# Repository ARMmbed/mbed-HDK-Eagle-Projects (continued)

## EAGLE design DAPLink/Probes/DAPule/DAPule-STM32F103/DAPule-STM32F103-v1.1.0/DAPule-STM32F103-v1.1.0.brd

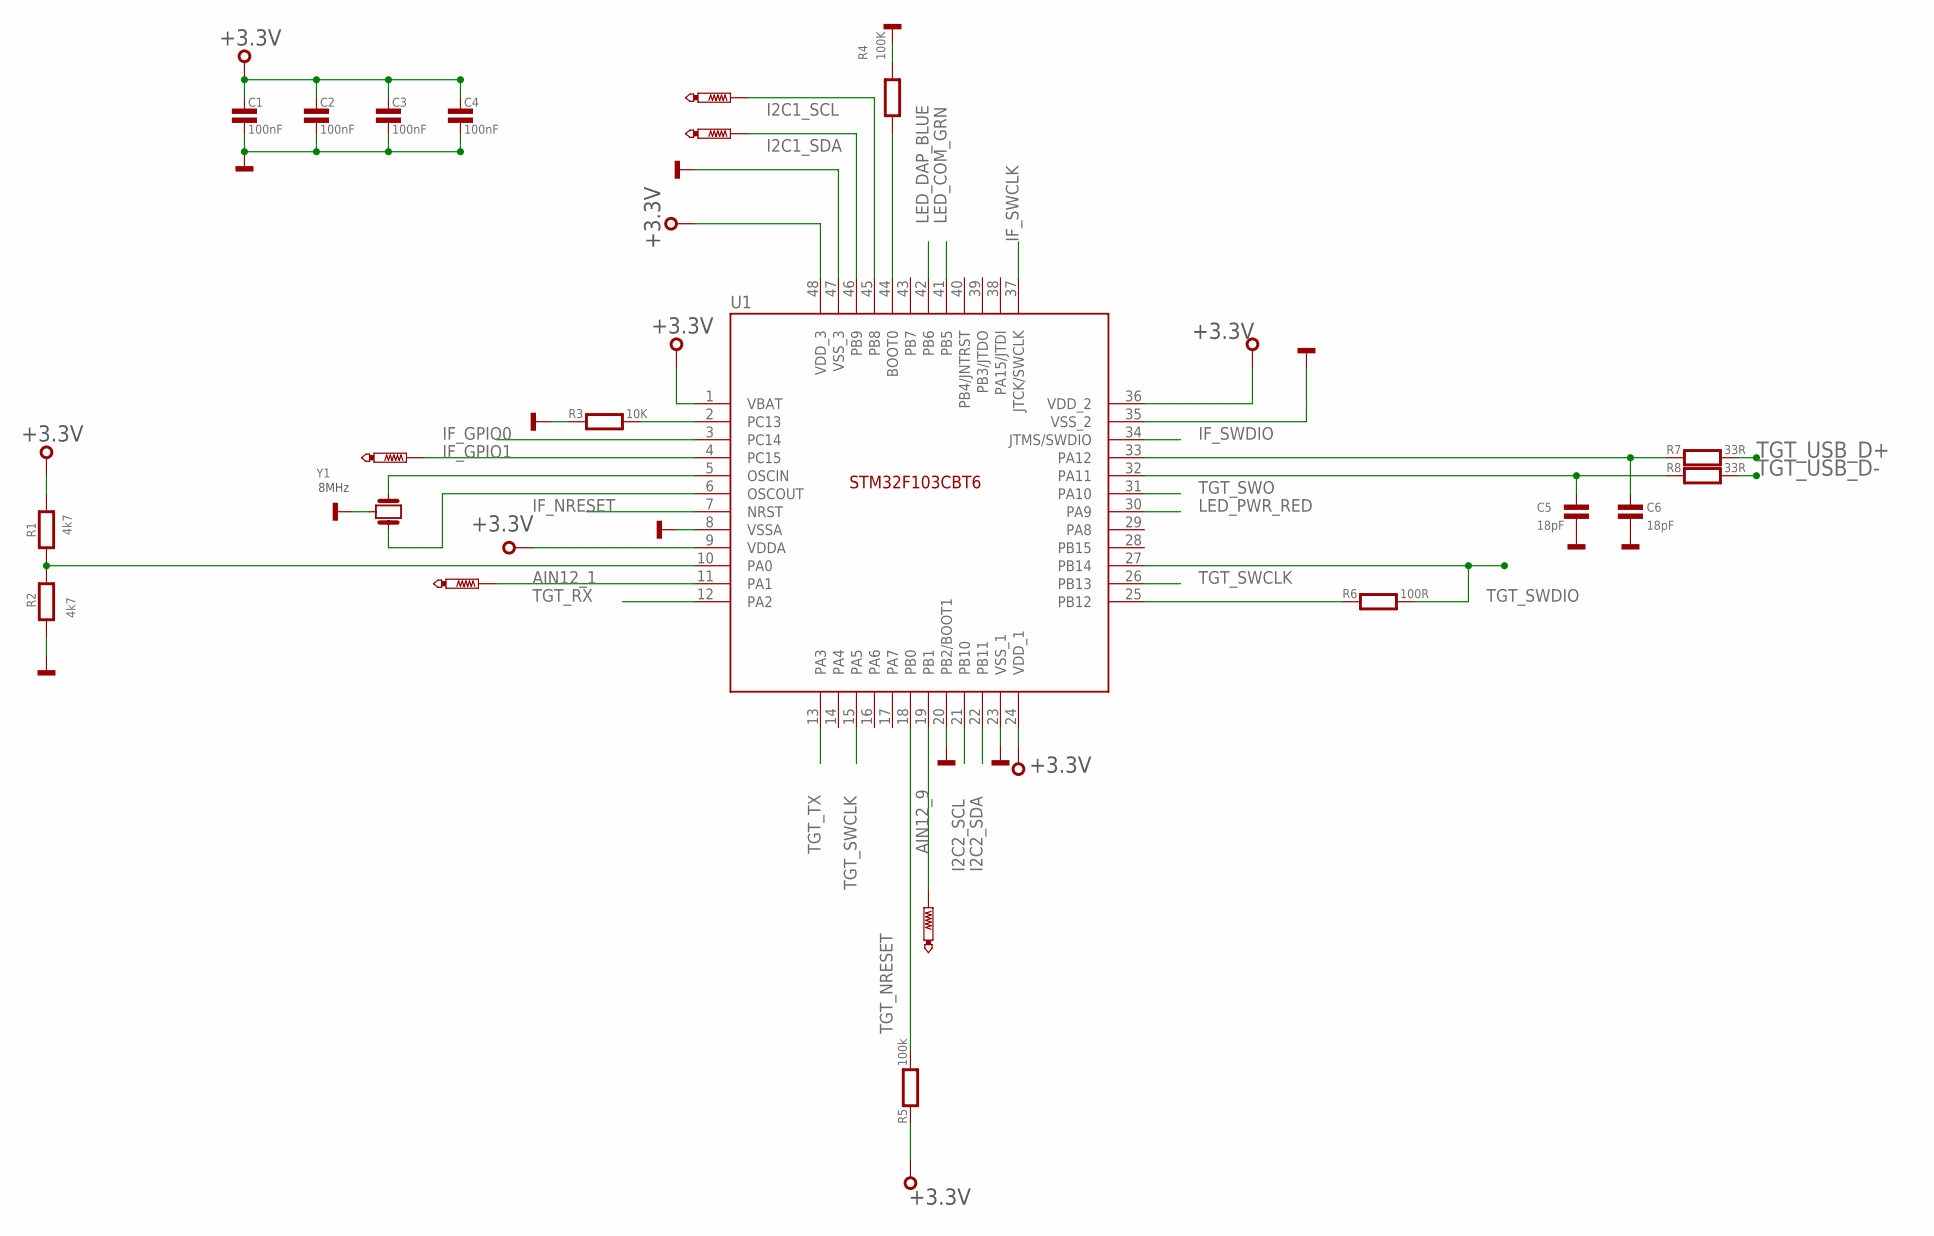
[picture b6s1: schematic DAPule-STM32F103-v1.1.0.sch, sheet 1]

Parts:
C1, C2, C3, C4: 100nF; 0603
C5, C6: 18pF; 0603
R1, R2: 4k7; 0603
R3: 10K; 0603
R4: 100K; 0603
R5: 100k; 0603
R6: 100R; 0603
R7, R8: 33R; 0603
TP1, TP2, TP3, TP4, TP5: PTR1TP07R; TP07R
U1: STM32F103CBT6; LQFP48
Y1: CSTCE8M00G55-R0

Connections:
+3.3V: C1.1, C2.1, C3.1, C4.1, R1.1, R5.1, U1.1 (VBAT), U1.9 (VDDA), U1.24 (VDD_1), U1.36 (VDD_2), U1.48 (VDD_3); also elsewhere on the board
AIN12_1: TP2.TP, U1.11 (PA1)
AIN12_9: TP1.TP, U1.19 (PB1)
GND: C1.2, C2.2, C3.2, C4.2, C5.2, C6.2, R2.2, R3.1, R4.1, U1.8 (VSSA), U1.20 (PB2/BOOT1), U1.23 (VSS_1), U1.35 (VSS_2), U1.47 (VSS_3), Y1.2; also elsewhere on the board
I2C1_SCL: TP4.TP, U1.45 (PB8)
I2C1_SDA: TP5.TP, U1.46 (PB9)
I2C2_SCL: U1.21 (PB10); also elsewhere on the board
I2C2_SDA: U1.22 (PB11); also elsewhere on the board
IF_GPIO0: U1.3 (PC14); also elsewhere on the board
IF_GPIO1: TP3.TP, U1.4 (PC15)
IF_NRESET: U1.7 (NRST); also elsewhere on the board
IF_SWCLK: U1.37 (JTCK/SWCLK); also elsewhere on the board
IF_SWDIO: U1.34 (JTMS/SWDIO); also elsewhere on the board
LED_COM_GRN: U1.41 (PB5); also elsewhere on the board
LED_DAP_BLUE: U1.42 (PB6); also elsewhere on the board
LED_PWR_RED: U1.30 (PA9); also elsewhere on the board
unnamed: R4.2, U1.44 (BOOT0)
unnamed: R3.2, U1.2 (PC13)
unnamed: U1.6 (OSCOUT), Y1.3
unnamed: U1.5 (OSCIN), Y1.1
unnamed: R1.2, R2.1, U1.10 (PA0)
unnamed: R6.1, U1.25 (PB12)
unnamed: C6.1, R7.1, U1.33 (PA12)
unnamed: C5.1, R8.1, U1.32 (PA11)
TGT_NRESET: R5.2, U1.18 (PB0); also elsewhere on the board
TGT_RX: U1.12 (PA2); also elsewhere on the board
TGT_SWCLK: U1.15 (PA5), U1.26 (PB13); also elsewhere on the board
TGT_SWDIO: R6.2, U1.27 (PB14); also elsewhere on the board
TGT_SWO: U1.31 (PA10); also elsewhere on the board
TGT_TX: U1.13 (PA3); also elsewhere on the board
TGT_USB_D+: R7.2; also elsewhere on the board
TGT_USB_D-: R8.2; also elsewhere on the board

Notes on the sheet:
8MHz

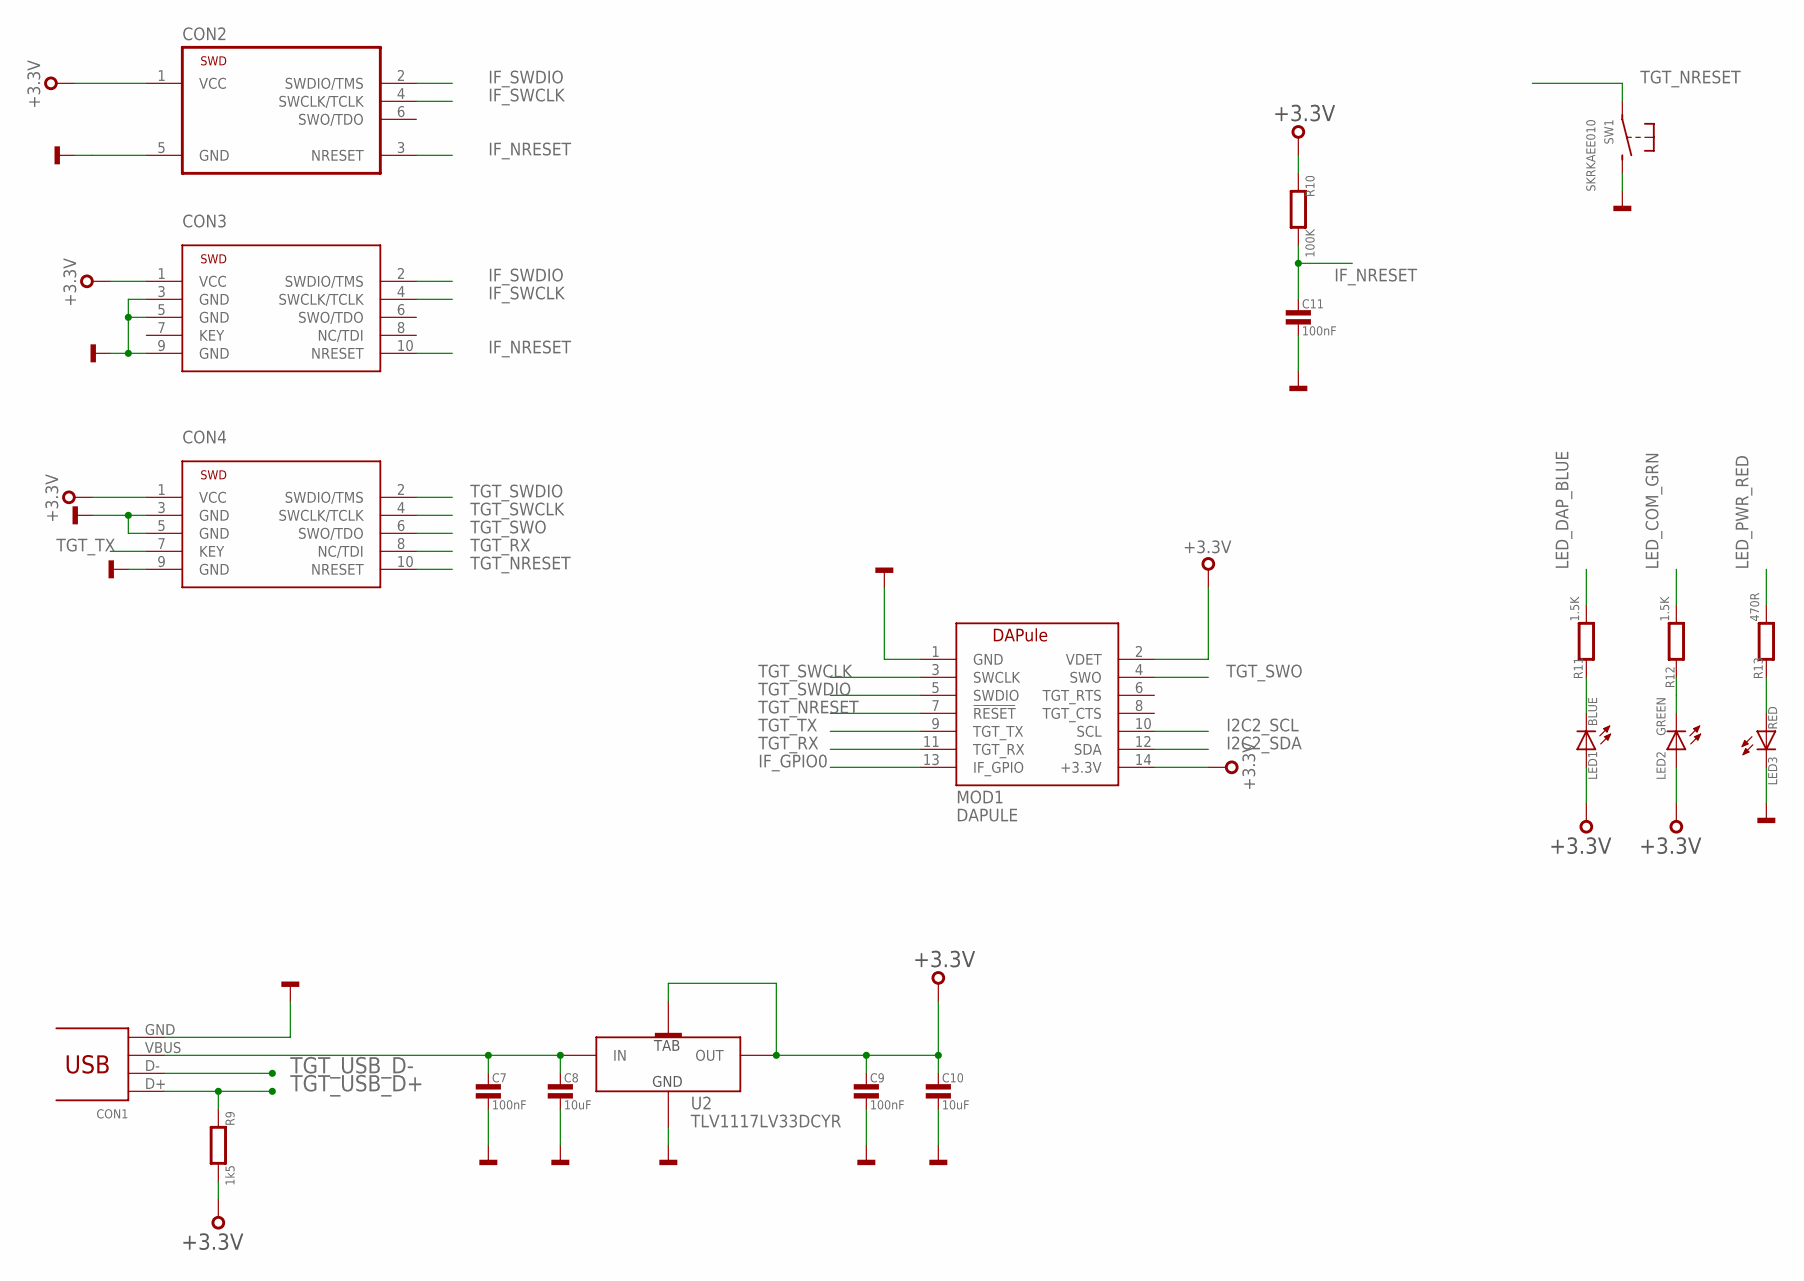
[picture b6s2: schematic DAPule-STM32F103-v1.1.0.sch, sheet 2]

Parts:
C7, C9, C11: 100nF; 0603
C8, C10: 10uF; 0603
CON1: 47346-0001; USB-MICRO-B-H
CON2: TC2030-CTX-NL
CON3, CON4: SWD-10-SMD
LED1: BLUE; CHIPLED_0603
LED2: GREEN; CHIPLED_0603
LED3: RED; CHIPLED_0603
MOD1: DAPULE
R9: 1k5; 0603
R10: 100K; 0603
R11, R12: 1.5K; 0603
R13: 470R; 0603
SW1: SKRKAEE010
U2: TLV1117LV33DCYR; SOT223

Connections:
+3.3V: C9.1, C10.1, CON2.1 (VCC), CON3.1 (VCC), CON4.1 (VCC), LED1.A, LED2.A, MOD1.2 (VDET), MOD1.14 (+3.3V), R9.2, R10.1, U2.OUT(1) (OUT), U2.OUT(2) (TAB); also elsewhere on the board
GND: C7.2, C8.2, C9.2, C10.2, C11.2, CON1.GND, CON2.5 (GND), CON3.3 (GND), CON3.5 (GND), CON3.9 (GND), CON4.3 (GND), CON4.5 (GND), CON4.9 (GND), LED3.C, MOD1.1 (GND), SW1.P$2 (S), U2.GND; also elsewhere on the board
I2C2_SCL: MOD1.10 (SCL); also elsewhere on the board
I2C2_SDA: MOD1.12 (SDA); also elsewhere on the board
IF_GPIO0: MOD1.13 (IF_GPIO); also elsewhere on the board
IF_NRESET: C11.1, CON2.3 (NRESET), CON3.10 (NRESET), R10.2; also elsewhere on the board
IF_SWCLK: CON2.4 (SWCLK/TCLK), CON3.4 (SWCLK/TCLK); also elsewhere on the board
IF_SWDIO: CON2.2 (SWDIO/TMS), CON3.2 (SWDIO/TMS); also elsewhere on the board
LED_COM_GRN: R12.2; also elsewhere on the board
LED_DAP_BLUE: R11.2; also elsewhere on the board
LED_PWR_RED: R13.2; also elsewhere on the board
unnamed: C7.1, C8.1, CON1.VBUS, U2.IN
unnamed: LED3.A, R13.1
unnamed: LED1.C, R11.1
unnamed: LED2.C, R12.1
TGT_NRESET: CON4.10 (NRESET), MOD1.7 (!RESET), SW1.P$1; also elsewhere on the board
TGT_RX: CON4.8 (NC/TDI), MOD1.11 (TGT_RX); also elsewhere on the board
TGT_SWCLK: CON4.4 (SWCLK/TCLK), MOD1.3 (SWCLK); also elsewhere on the board
TGT_SWDIO: CON4.2 (SWDIO/TMS), MOD1.5 (SWDIO); also elsewhere on the board
TGT_SWO: CON4.6 (SWO/TDO), MOD1.4 (SWO); also elsewhere on the board
TGT_TX: CON4.7 (KEY), MOD1.9 (TGT_TX); also elsewhere on the board
TGT_USB_D+: CON1.D+, R9.1; also elsewhere on the board
TGT_USB_D-: CON1.D-; also elsewhere on the board

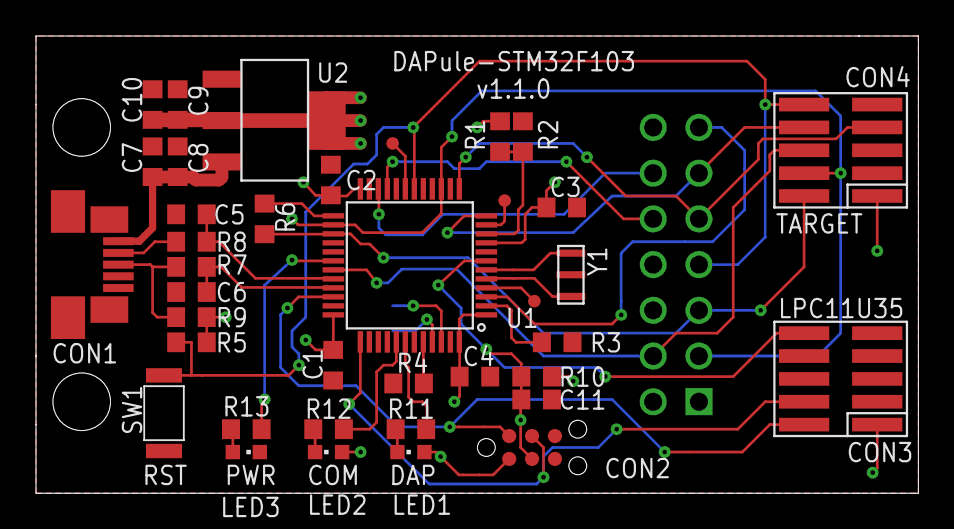
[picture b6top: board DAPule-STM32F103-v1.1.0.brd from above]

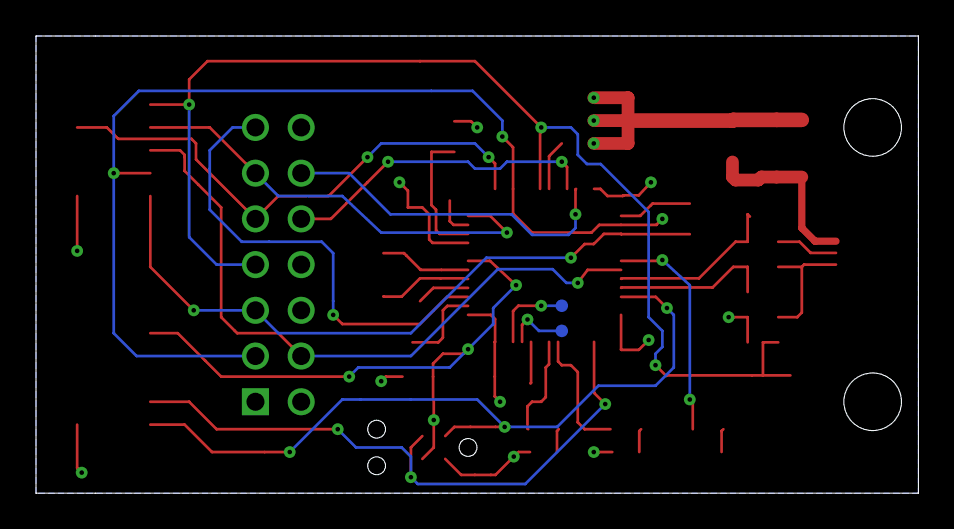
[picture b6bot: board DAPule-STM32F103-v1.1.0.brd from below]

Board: 2 copper layers, 49.0 x 25.4 mm, 41 parts (2 on the bottom side), 36 nets.

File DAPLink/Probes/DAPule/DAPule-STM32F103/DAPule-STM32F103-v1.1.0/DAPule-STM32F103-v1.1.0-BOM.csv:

"Qty";"Value";"Device";"Package";"Parts";"Description";"MF";"MFN";"OC-DIGIKEY";"OC-MOUSER";"OC-NEWARK";"TP_SIGNAL_NAME";
"2";"1.5K";"R0603";"0603";"R11, R12";"Resistor";"";"";"";"";"";"";
"2";"100K";"R0603";"0603";"R4, R10";"Resistor";"";"";"";"";"";"";
"1";"100R";"R0603";"0603";"R6";"Resistor";"";"";"";"";"";"";
"1";"100k";"R0603";"0603";"R5";"Resistor";"";"";"";"";"";"";
"7";"100nF";"C0603";"0603";"C1, C2, C3, C4, C7, C9, C11";"Capacitor";"";"";"";"";"";"";
"1";"10K";"R0603";"0603";"R3";"Resistor";"";"";"";"";"";"";
"2";"10uF";"C0603";"0603";"C8, C10";"Capacitor";"";"";"";"";"";"";
"2";"18pF";"C0603";"0603";"C5, C6";"Capacitor";"";"";"";"";"";"";
"1";"1k5";"R0603";"0603";"R9";"Resistor";"";"";"";"";"";"";
"2";"33R";"R0603";"0603";"R7, R8";"Resistor";"";"";"";"";"";"";
"1";"470R";"R0603";"0603";"R13";"Resistor";"";"";"";"";"";"";
"1";"47346-0001";"47346-0001";"USB-MICRO-B-H";"CON1";"USB Receptacle Horizontal Micro Type B";"MOLEX";"47346-0001";"";"538-47346-0001";"1568026";"";
"2";"4k7";"R0603";"0603";"R1, R2";"Resistor";"";"";"";"";"";"";
"1";"BLUE";"SMD_LED0603";"CHIPLED_0603";"LED1";"LED SMD, Colour Red";"Wurth Electronics Inc";"150060RS75000";"732-4978-1-ND";"710-150060RS75000";"2322071";"";
"1";"CSTCE8M00G55-R0";"CSTCE8M00G55-R0";"CSTCE8M00G55-R0";"Y1";"Resonator Cermanic, Murata 8MHz 33pF";"Murata";"CSTCE8M00G55-R0";"490-1195-1-ND";"81-CSTCE8M00G55-R0";"2443270";"";
"1";"DAPULE";"DAPULE";"DAPULE";"MOD1";"";"";"";"";"";"";"";
"1";"GREEN";"SMD_LED0603";"CHIPLED_0603";"LED2";"LED SMD, Colour Red";"Wurth Electronics Inc";"150060RS75000";"732-4978-1-ND";"710-150060RS75000";"2322071";"";
"5";"PTR1TP07R";"PTR1TP07R";"TP07R";"TP1, TP2, TP3, TP4, TP5";"TEST PIN";"";"";"";"";"";"";
"1";"RED";"SMD_LED0603";"CHIPLED_0603";"LED3";"LED SMD, Colour Red";"Wurth Electronics Inc";"150060RS75000";"732-4978-1-ND";"710-150060RS75000";"2322071";"";
"1";"SKRKAEE010";"SKRKAEE010";"SKRKAEE010";"SW1";"MOMENTARY SWITCH PUSH VERTICAL (SPST)";"ALPS";"SKRKAEE010";"";"688-SKRKAE";"";"";
"1";"STM32F103CBT6";"STM32F103CBT6";"LQFP48";"U1";"ARM® Cortex®-M3 STM32 F1 Microcontroller IC 32-Bit 72MHz 128KB (128K x 8) FLASH";"STMicroelectronics";"STM32F103CBT6";"497-6288-ND";"511-STM32F103CBT6";"11N8296";"";
"2";"SWD-10-SMD";"SWD-10-SMD";"SWD-10-SMD";"CON3, CON4";"2.54mm pitch 10-Pin Cortex Programming Header";"";"";"";"";"";"";
"1";"TC2030-CTX-NL";"TC2030-CTX-NL";"TC2030-CTX-NL";"CON2";"Tag-Connect In Circuit Programming & Debug Cable 6 Pin";"";"";"";"";"";"";
"1";"TLV1117LV33DCYR";"TLV1117LV33DCYR";"SOT223";"U2";"LDO Fixed Regulator 3.3v, 1A";"Texas Instruments";"TLV1117LV33DCYR";"296-28778-1-ND";"595-TLV1117LV33DCYR";"2323647";"";

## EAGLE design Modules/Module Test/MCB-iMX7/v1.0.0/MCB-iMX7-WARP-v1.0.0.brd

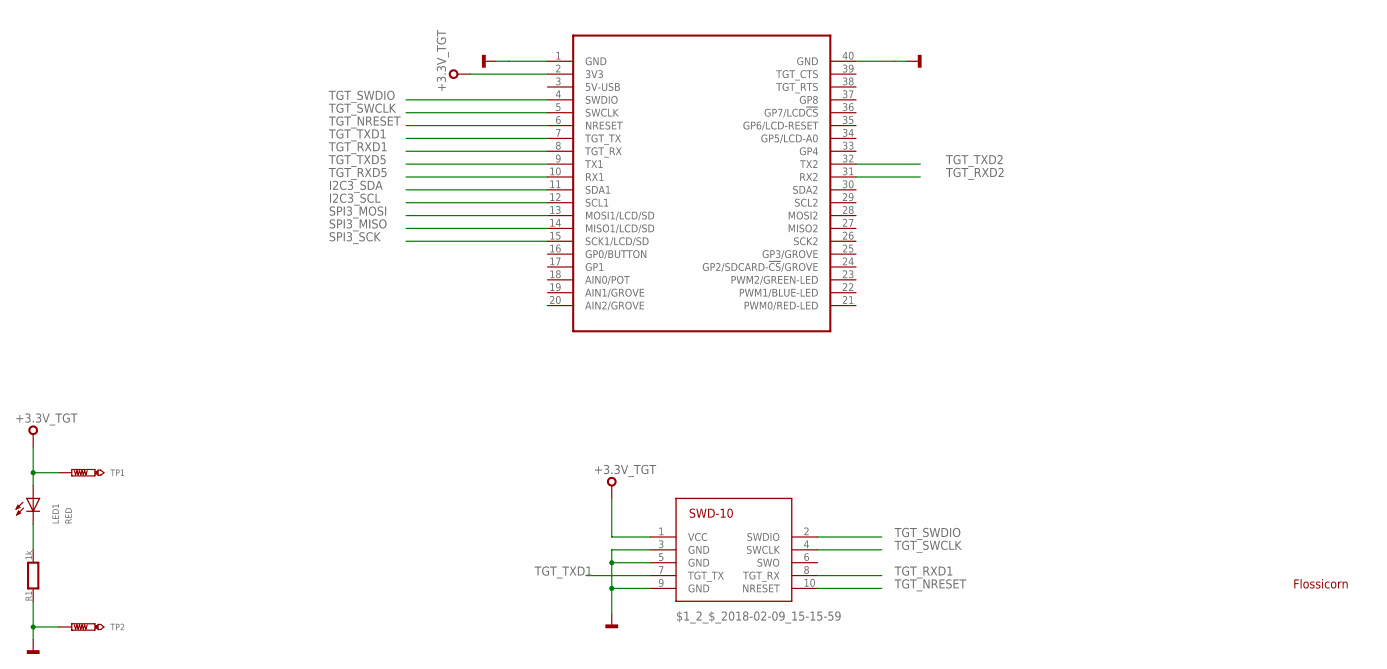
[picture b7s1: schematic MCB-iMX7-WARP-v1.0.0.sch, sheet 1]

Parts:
$1_2_$_2018-02-09_15-15-59: SWD-10/TC2050_SMD; FTSH-105-02
LED1: RED; CHIPLED_0603
MOD1: MODULE_DAUGHTER
R1: 1k; 0603
SS1: FLOSSICORN0.5; FLOSSICORN-0.5
TP1, TP2: TEST-POINT-50R-PTH; TP50-PTH

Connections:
+3.3V_TGT: $1_2_$_2018-02-09_15-15-59.1 (VCC), LED1.A, MOD1.2 (3V3), TP1.TP; also elsewhere on the board
GND: $1_2_$_2018-02-09_15-15-59.3 (GND), $1_2_$_2018-02-09_15-15-59.5 (GND), $1_2_$_2018-02-09_15-15-59.9 (GND), MOD1.1 (GND), MOD1.40 (GND), R1.1, TP2.TP; also elsewhere on the board
I2C3_SCL: MOD1.12 (SCL1); also elsewhere on the board
I2C3_SDA: MOD1.11 (SDA1); also elsewhere on the board
PA_1: LED1.C, R1.2
SPI3_MISO: MOD1.14 (MISO1/LCD/SD); also elsewhere on the board
SPI3_MOSI: MOD1.13 (MOSI1/LCD/SD); also elsewhere on the board
SPI3_SCK: MOD1.15 (SCK1/LCD/SD); also elsewhere on the board
TGT_NRESET: $1_2_$_2018-02-09_15-15-59.10 (NRESET), MOD1.6 (NRESET)
TGT_RXD1: $1_2_$_2018-02-09_15-15-59.8 (TGT_RX), MOD1.8 (TGT_RX); also elsewhere on the board
TGT_RXD2: MOD1.31 (RX2); also elsewhere on the board
TGT_RXD5: MOD1.10 (RX1); also elsewhere on the board
TGT_SWCLK: $1_2_$_2018-02-09_15-15-59.4 (SWCLK), MOD1.5 (SWCLK); also elsewhere on the board
TGT_SWDIO: $1_2_$_2018-02-09_15-15-59.2 (SWDIO), MOD1.4 (SWDIO); also elsewhere on the board
TGT_TXD1: $1_2_$_2018-02-09_15-15-59.7 (TGT_TX), MOD1.7 (TGT_TX); also elsewhere on the board
TGT_TXD2: MOD1.32 (TX2); also elsewhere on the board
TGT_TXD5: MOD1.9 (TX1); also elsewhere on the board

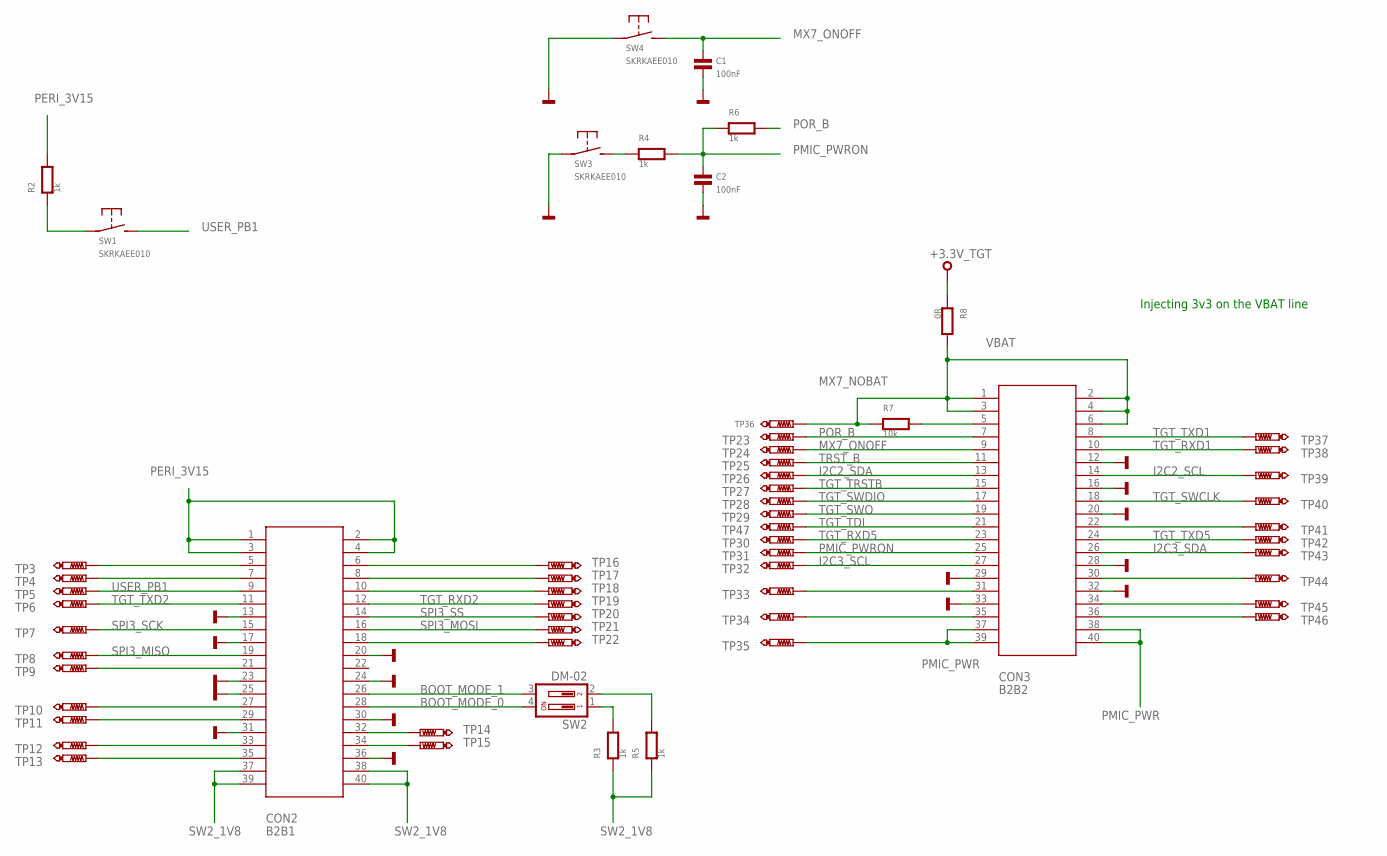
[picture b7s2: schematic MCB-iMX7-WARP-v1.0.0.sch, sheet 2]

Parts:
C1, C2: 100nF; 0603
CON2: B2B1; DF40HC-XX-40DS-XX-V
CON3: B2B2; DF40HC-XX-40DS-XX-V
R2, R3, R4, R5, R6: 1k; 0603
R7: 10k; 0603
R8: 0R; 0603
SW1, SW3, SW4: SKRKAEE010
SW2: DM-02
TP3, TP4, TP5, TP6, TP7, TP8, TP9, TP10, TP11, TP12, TP13, TP14, TP15, TP16, TP17, TP18, TP19, TP20, TP21, TP22, TP23, TP24, TP25, TP26, TP27, TP28, TP29, TP30, TP31, TP32, TP33, TP34, TP37, TP38, TP39, TP40, TP41, TP42, TP43, TP44, TP45, TP46, TP47: PTR1TP06R; TP06R
TP35: PTR1TP10R; TP10R
TP36: TEST-POINT-50R-SMD; TP50-SMD

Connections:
+3.3V_TGT: R8.1; also elsewhere on the board
BOOT_MODE_0: CON2.28, SW2.4
BOOT_MODE_1: CON2.26, SW2.3
GND: C1.2, C2.2, CON2.13, CON2.17, CON2.20, CON2.23, CON2.24, CON2.25, CON2.30, CON2.31, CON2.36, CON3.12, CON3.16, CON3.20, CON3.28, CON3.29, CON3.32, CON3.33, SW3.P$1, SW4.P$1; also elsewhere on the board
I2C2_SCL: CON3.14, TP39.TP
I2C2_SDA: CON3.13, TP26.TP
I2C3_SCL: CON3.27, TP32.TP; also elsewhere on the board
I2C3_SDA: CON3.26, TP43.TP; also elsewhere on the board
MX7_NOBAT: CON3.5, R7.2
MX7_ONOFF: C1.1, CON3.9, SW4.P$2 (S), TP24.TP
unnamed: R4.1, SW3.P$2 (S)
unnamed: R2.1, SW1.P$1
unnamed: CON3.36, TP46.TP
unnamed: CON3.22, TP41.TP
unnamed: CON3.30, TP44.TP
unnamed: CON3.34, TP45.TP
unnamed: R3.2, SW2.1
unnamed: R5.2, SW2.2
unnamed: CON3.31, TP33.TP
unnamed: CON3.35, TP34.TP
unnamed: CON2.5, TP3.TP
unnamed: CON2.7, TP4.TP
unnamed: CON2.21, TP9.TP
unnamed: CON2.27, TP10.TP
unnamed: CON2.29, TP11.TP
unnamed: CON2.33, TP12.TP
unnamed: CON2.35, TP13.TP
unnamed: CON2.34, TP15.TP
unnamed: CON2.32, TP14.TP
unnamed: CON2.18, TP22.TP
unnamed: CON2.10, TP18.TP
unnamed: CON2.8, TP17.TP
unnamed: CON2.6, TP16.TP
PERI_3V15: CON2.1, CON2.2, CON2.3, CON2.4, R2.2
PMIC_PWR: CON3.37, CON3.38, CON3.39, CON3.40, TP35.TP
PMIC_PWRON: C2.1, CON3.25, R4.2, R6.1, TP31.TP
POR_B: CON3.7, R6.2, TP23.TP
SPI3_MISO: CON2.19, TP8.TP; also elsewhere on the board
SPI3_MOSI: CON2.16, TP21.TP; also elsewhere on the board
SPI3_SCK: CON2.15, TP7.TP; also elsewhere on the board
SPI3_SS: CON2.14, TP20.TP
SW2_1V8: CON2.37, CON2.38, CON2.39, CON2.40, R3.1, R5.1
TGT_RXD1: CON3.10, TP38.TP; also elsewhere on the board
TGT_RXD2: CON2.12, TP19.TP; also elsewhere on the board
TGT_RXD5: CON3.23, TP30.TP; also elsewhere on the board
TGT_SWCLK: CON3.18, TP40.TP; also elsewhere on the board
TGT_SWDIO: CON3.17, TP28.TP; also elsewhere on the board
TGT_SWO: CON3.19, TP29.TP
TGT_TDI: CON3.21, TP47.TP
TGT_TRSTB: CON3.15, TP27.TP
TGT_TXD1: CON3.8, TP37.TP; also elsewhere on the board
TGT_TXD2: CON2.11, TP6.TP; also elsewhere on the board
TGT_TXD5: CON3.24, TP42.TP; also elsewhere on the board
TRST_B: CON3.11, TP25.TP
USER_PB1: CON2.9, SW1.P$2 (S), TP5.TP
VBAT: CON3.1, CON3.2, CON3.3, CON3.4, CON3.6, R7.1, R8.2, TP36.TP

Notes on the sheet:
Injecting 3v3 on the VBAT line

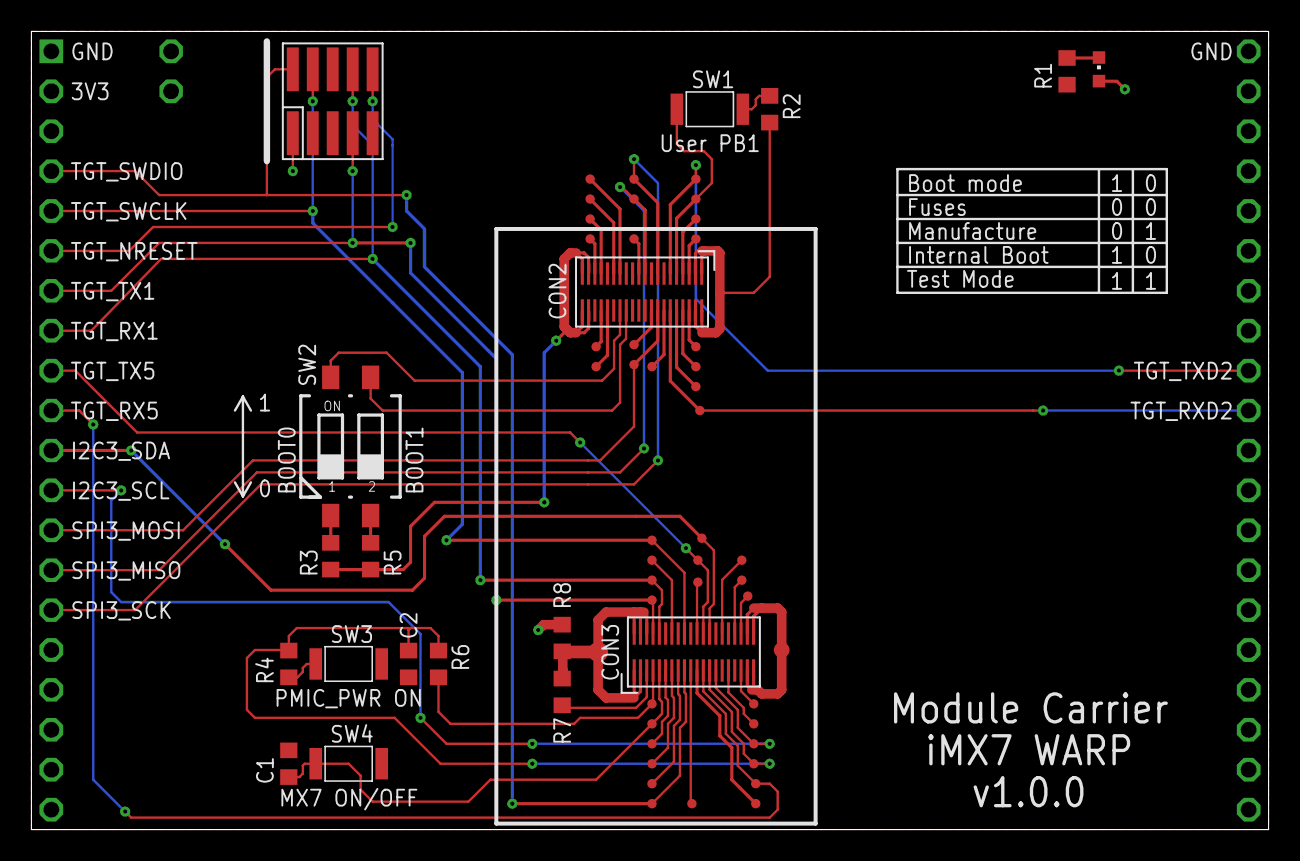
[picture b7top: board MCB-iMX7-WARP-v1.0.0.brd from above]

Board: 2 copper layers, 78.7 x 50.8 mm, 67 parts (0 on the bottom side), 58 nets.

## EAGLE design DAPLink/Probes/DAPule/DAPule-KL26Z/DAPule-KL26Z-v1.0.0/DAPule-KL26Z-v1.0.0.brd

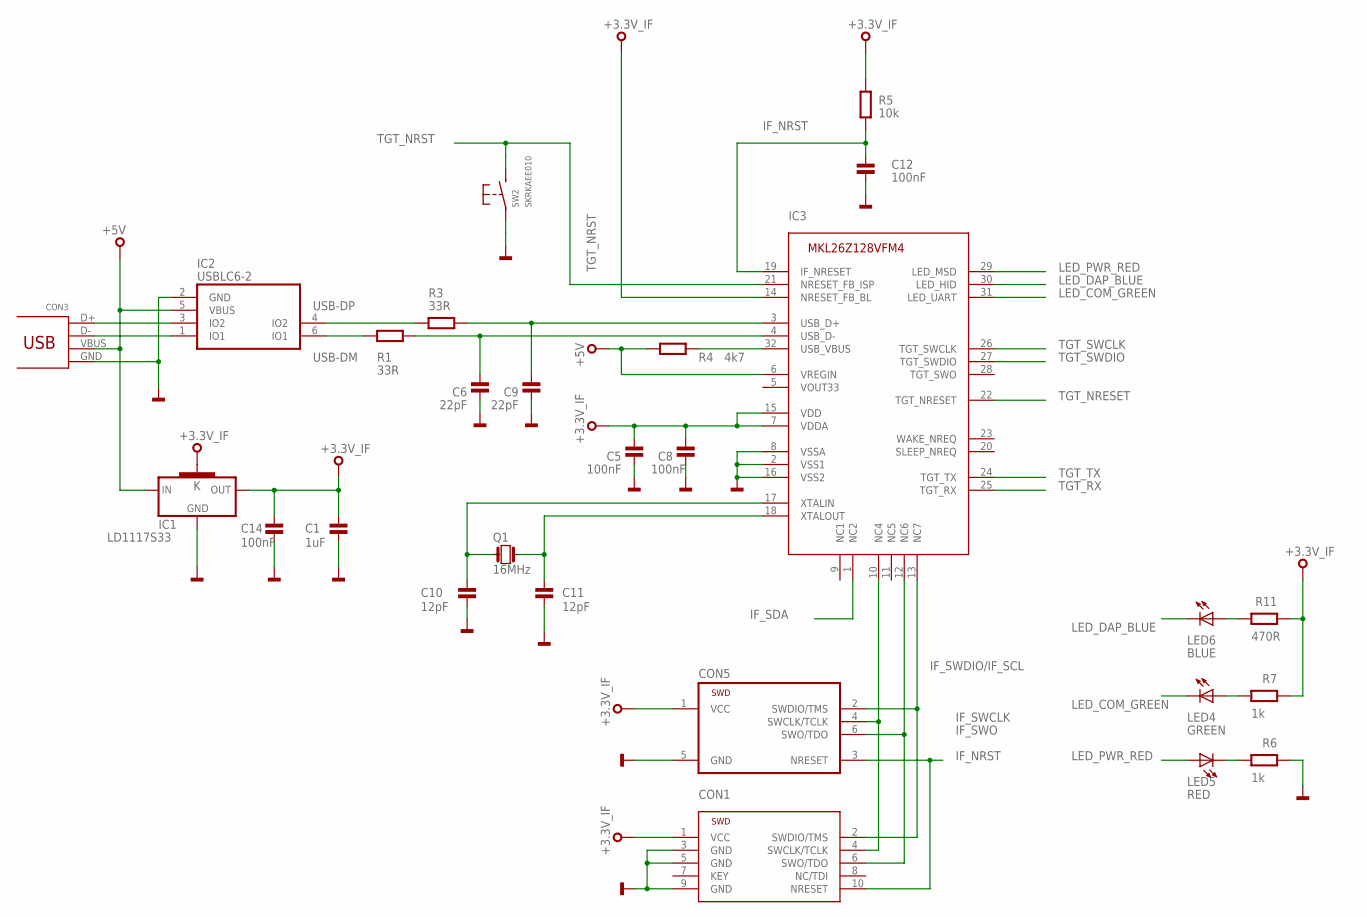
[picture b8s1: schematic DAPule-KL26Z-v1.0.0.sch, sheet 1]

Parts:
C1: 1uF; 0603
C5, C8, C12, C14: 100nF; 0603
C6, C9: 22pF; 0603
C10, C11: 12pF; 0603
CON1: SWD-10-SMD
CON3: USB_MICROB; MOLEX-47364-0001
CON5: TC2030-CTX-NL
IC1: LD1117S33; SOT223
IC2: USBLC6-2SC6; SOT23-6L
IC3: IF_MKL26Z128VFM4; HVQFN32
LED4: GREEN; CHIPLED_0603
LED5: RED; CHIPLED_0603
LED6: BLUE; CHIPLED_0603
Q1: 16MHz; 2.5X2.0
R1, R3: 33R; 0603@1
R4: 4k7; 0603@1
R5: 10k; 0603@1
R6, R7: 1k; 0603@1
R11: 470R; 0603@1
SW2: SKRKAEE010

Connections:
+3.3V_IF: C1.1, C5.2, C8.2, C14.1, CON1.1 (VCC), CON5.1 (VCC), IC1.2 (OUT), IC1.4 (K), IC3.7 (VDDA), IC3.14 (NRESET_FB_BL), IC3.15 (VDD), R5.2, R7.1, R11.1; also elsewhere on the board
+5V: CON3.VBUS, IC1.3 (IN), IC2.5 (VBUS), IC3.6 (VREGIN), R4.1
DM: CON3.D-, IC2.1 (IO1)
DP: CON3.D+, IC2.3 (IO2)
GND: C1.2, C5.1, C6.1, C8.1, C9.1, C10.1, C11.1, C12.1, C14.2, CON1.3 (GND), CON1.5 (GND), CON1.9 (GND), CON3.GND, CON5.5 (GND), IC1.1 (GND), IC2.2 (GND), IC3.2 (VSS1), IC3.8 (VSSA), IC3.16 (VSS2), R6.1, SW2.P$1; also elsewhere on the board
IF_NRST: C12.2, CON1.10 (NRESET), CON5.3 (NRESET), IC3.19 (IF_NRESET), R5.1
IF_SDA: IC3.1 (NC2); also elsewhere on the board
IF_SWCLK: CON1.4 (SWCLK/TCLK), CON5.4 (SWCLK/TCLK), IC3.10 (NC4)
IF_SWDIO/IF_SCL: CON1.2 (SWDIO/TMS), CON5.2 (SWDIO/TMS), IC3.13 (NC7); also elsewhere on the board
IF_SWO: CON1.6 (SWO/TDO), CON5.6 (SWO/TDO), IC3.12 (NC6)
LED_COM_GREEN: IC3.31 (LED_UART), LED4.C
LED_DAP_BLUE: IC3.30 (LED_HID), LED6.C
LED_PWR_RED: IC3.29 (LED_MSD), LED5.A
unnamed: IC3.32 (USB_VBUS), R4.2
unnamed: LED6.A, R11.2
unnamed: LED4.A, R7.2
unnamed: C6.2, IC3.4 (USB_D-), R1.1
unnamed: C10.2, IC3.17 (XTALIN), Q1.1
unnamed: C11.2, IC3.18 (XTALOUT), Q1.3 (2)
unnamed: C9.2, IC3.3 (USB_D+), R3.1
unnamed: LED5.C, R6.2
TGT_NRESET: IC3.22 (TGT_NRESET); also elsewhere on the board
TGT_NRST: IC3.21 (NRESET_FB_ISP), SW2.P$2 (S)
TGT_RX: IC3.25 (TGT_RX); also elsewhere on the board
TGT_SWCLK: IC3.26 (TGT_SWCLK); also elsewhere on the board
TGT_SWDIO: IC3.27 (TGT_SWDIO); also elsewhere on the board
TGT_TX: IC3.24 (TGT_TX); also elsewhere on the board
USB-DM: IC2.6 (IO1), R1.2
USB-DP: IC2.4 (IO2), R3.2

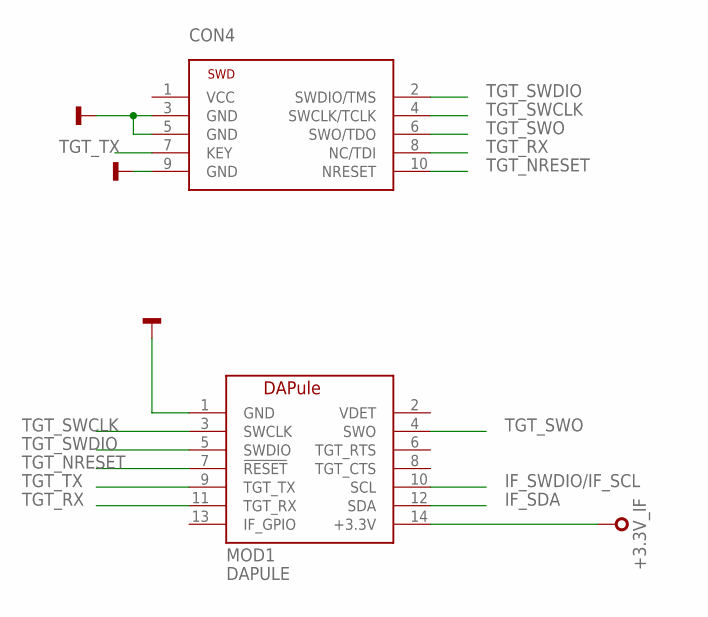
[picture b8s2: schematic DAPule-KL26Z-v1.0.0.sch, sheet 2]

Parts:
CON4: SWD-10-SMD
MOD1: DAPULE

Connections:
+3.3V_IF: MOD1.14 (+3.3V); also elsewhere on the board
GND: CON4.3 (GND), CON4.5 (GND), CON4.9 (GND), MOD1.1 (GND); also elsewhere on the board
IF_SDA: MOD1.12 (SDA); also elsewhere on the board
IF_SWDIO/IF_SCL: MOD1.10 (SCL); also elsewhere on the board
TGT_NRESET: CON4.10 (NRESET), MOD1.7 (!RESET); also elsewhere on the board
TGT_RX: CON4.8 (NC/TDI), MOD1.11 (TGT_RX); also elsewhere on the board
TGT_SWCLK: CON4.4 (SWCLK/TCLK), MOD1.3 (SWCLK); also elsewhere on the board
TGT_SWDIO: CON4.2 (SWDIO/TMS), MOD1.5 (SWDIO); also elsewhere on the board
TGT_SWO: CON4.6 (SWO/TDO), MOD1.4 (SWO)
TGT_TX: CON4.7 (KEY), MOD1.9 (TGT_TX); also elsewhere on the board

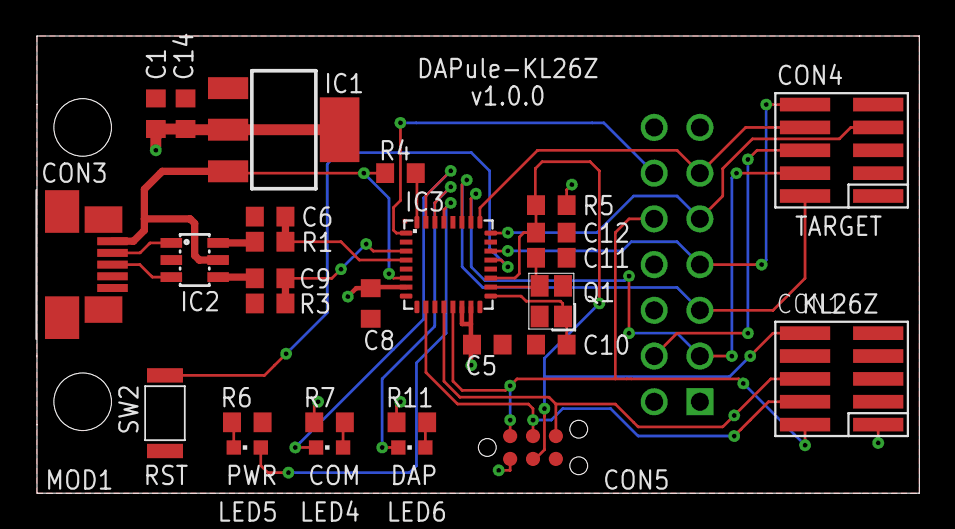
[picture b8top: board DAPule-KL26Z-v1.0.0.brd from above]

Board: 2 copper layers, 49.1 x 25.4 mm, 29 parts (0 on the bottom side), 30 nets.

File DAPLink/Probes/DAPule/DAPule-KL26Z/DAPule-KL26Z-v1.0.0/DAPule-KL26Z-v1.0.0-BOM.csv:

"Qty";"Value";"Device";"Package";"Parts";"Description";"MF";"MFN";"OC-DIGIKEY";"OC-MOUSER";"OC-NEWARK";
"4";"100nF";"C0603";"0603";"C5, C8, C12, C14";"Capacitor";"";"";"";"";"";
"1";"10k";"R0603";"0603@1";"R5";"";"";"";"";"";"";
"2";"12pF";"C0603";"0603";"C10, C11";"Capacitor";"";"";"";"";"";
"1";"16MHz";"Q_2.5X2.0";"2.5X2.0";"Q1";"";"";"";"";"";"";
"2";"1k";"R0603";"0603@1";"R6, R7";"";"";"";"";"";"";
"1";"1uF";"C0603";"0603";"C1";"Capacitor";"";"";"";"";"";
"2";"22pF";"C0603";"0603";"C6, C9";"Capacitor";"";"";"";"";"";
"2";"33R";"R0603";"0603@1";"R1, R3";"";"";"";"";"";"";
"1";"470R";"R0603";"0603@1";"R11";"";"";"";"";"";"";
"1";"4k7";"R0603";"0603@1";"R4";"";"";"";"";"";"";
"1";"BLUE";"LED0603";"CHIPLED_0603";"LED6";"SMD LED";"";"";"";"";"";
"1";"DAPULE";"DAPULE";"DAPULE";"MOD1";"";"";"";"";"";"";
"1";"GREEN";"LED0603";"CHIPLED_0603";"LED4";"SMD LED";"";"";"";"";"";
"1";"IF_MKL26Z128VFM4";"IF_MKL26Z128VFM4";"HVQFN32";"IC3";"CMSIS-DAP Interface (MK20DX128)";"";"";"";"";"";
"1";"LD1117S33";"LD1117S33";"SOT223";"IC1";"VOLTAGE REGULATOR SMD 3,3V";"";"";"";"";"";
"1";"RED";"LED0603";"CHIPLED_0603";"LED5";"SMD LED";"";"";"";"";"";
"1";"SKRKAEE010";"SKRKAEE010";"SKRKAEE010";"SW2";"MOMENTARY SWITCH PUSH VERTICAL (SPST)";"ALPS";"SKRKAEE010";"";"688-SKRKAE";"";
"2";"SWD-10-SMD";"SWD-10-SMD";"SWD-10-SMD";"CON1, CON4";"2.54mm pitch 10-Pin Cortex Programming Header";"";"";"";"";"";
"1";"TC2030-CTX-NL";"TC2030-CTX-NL";"TC2030-CTX-NL";"CON5";"Tag-Connect In Circuit Programming & Debug Cable 6 Pin";"";"";"";"";"";
"1";"USBLC6-2SC6";"USBLC6-2SC6";"SOT23-6L";"IC2";"";"";"";"";"";"";
"1";"USB_MICROB";"USB_MICROB";"MOLEX-47364-0001";"CON3";"USB Connectors";"";"";"";"";"";

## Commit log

2018-02-28 First check in of mbed-HDK-Eagle-Projects
2018-02-28 More reorganisation
2018-03-01 added SMD Mount files
2018-03-01 More reorganistion
2018-07-13 Updated to ignore zipfiles
2018-07-13 Refactor of repository
2018-09-17 Removing lots of stuff
2018-09-17 Add license to Modules directory
